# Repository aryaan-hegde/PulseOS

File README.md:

# PulseOS
A smartwatch that can detect, monitor and display your heart rate, show real time and calculate your daily steps. Contains a custom 4-layer, 35 mm circular PCB based on the RP2350B microcontroller with a heart-rate PPG sensor, RTC, IMU and TFT display. The smartwatch features a LiPo battery that can be charged through the PCB via a USB cable. Additionally, the board also contains a switchover mechanism so that you can power the watch solely through USB. Actively reduces battery consumption by turning off peripherals during idle mode (i.e. when stationary state is detected by the IMU).

The board routing can be seen below:

Additionally, a 3D model of this PCB is also shown below:
| Left Image | Right Image |
| :---: | :---: |
|  |

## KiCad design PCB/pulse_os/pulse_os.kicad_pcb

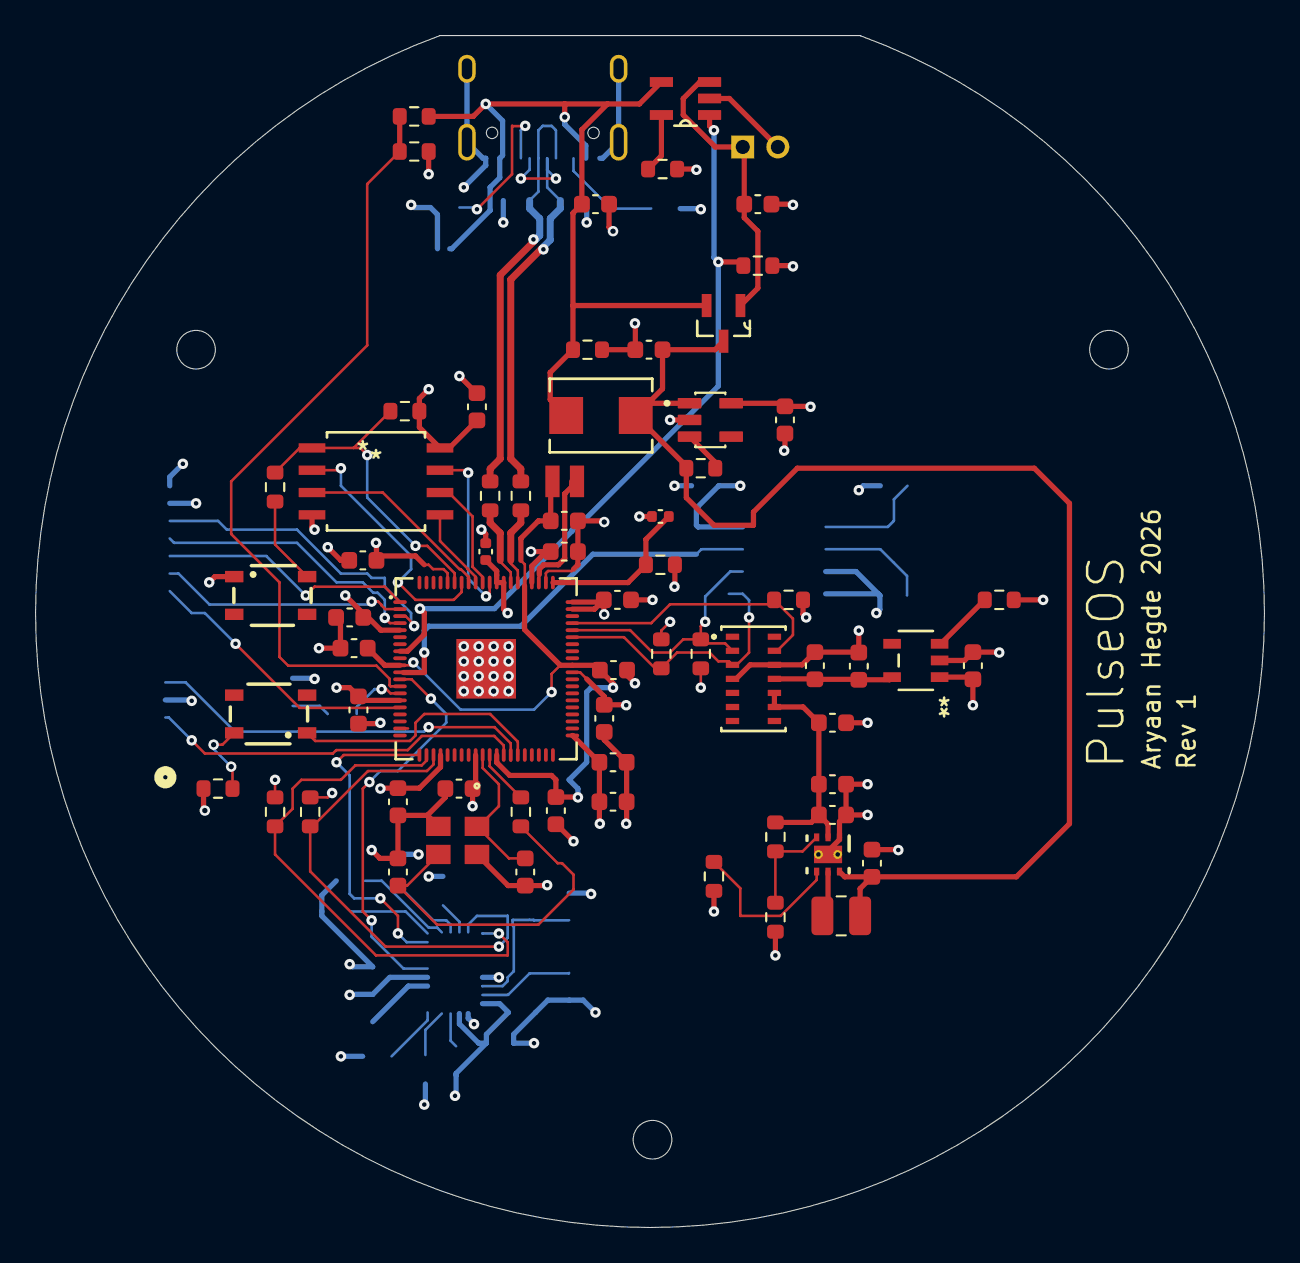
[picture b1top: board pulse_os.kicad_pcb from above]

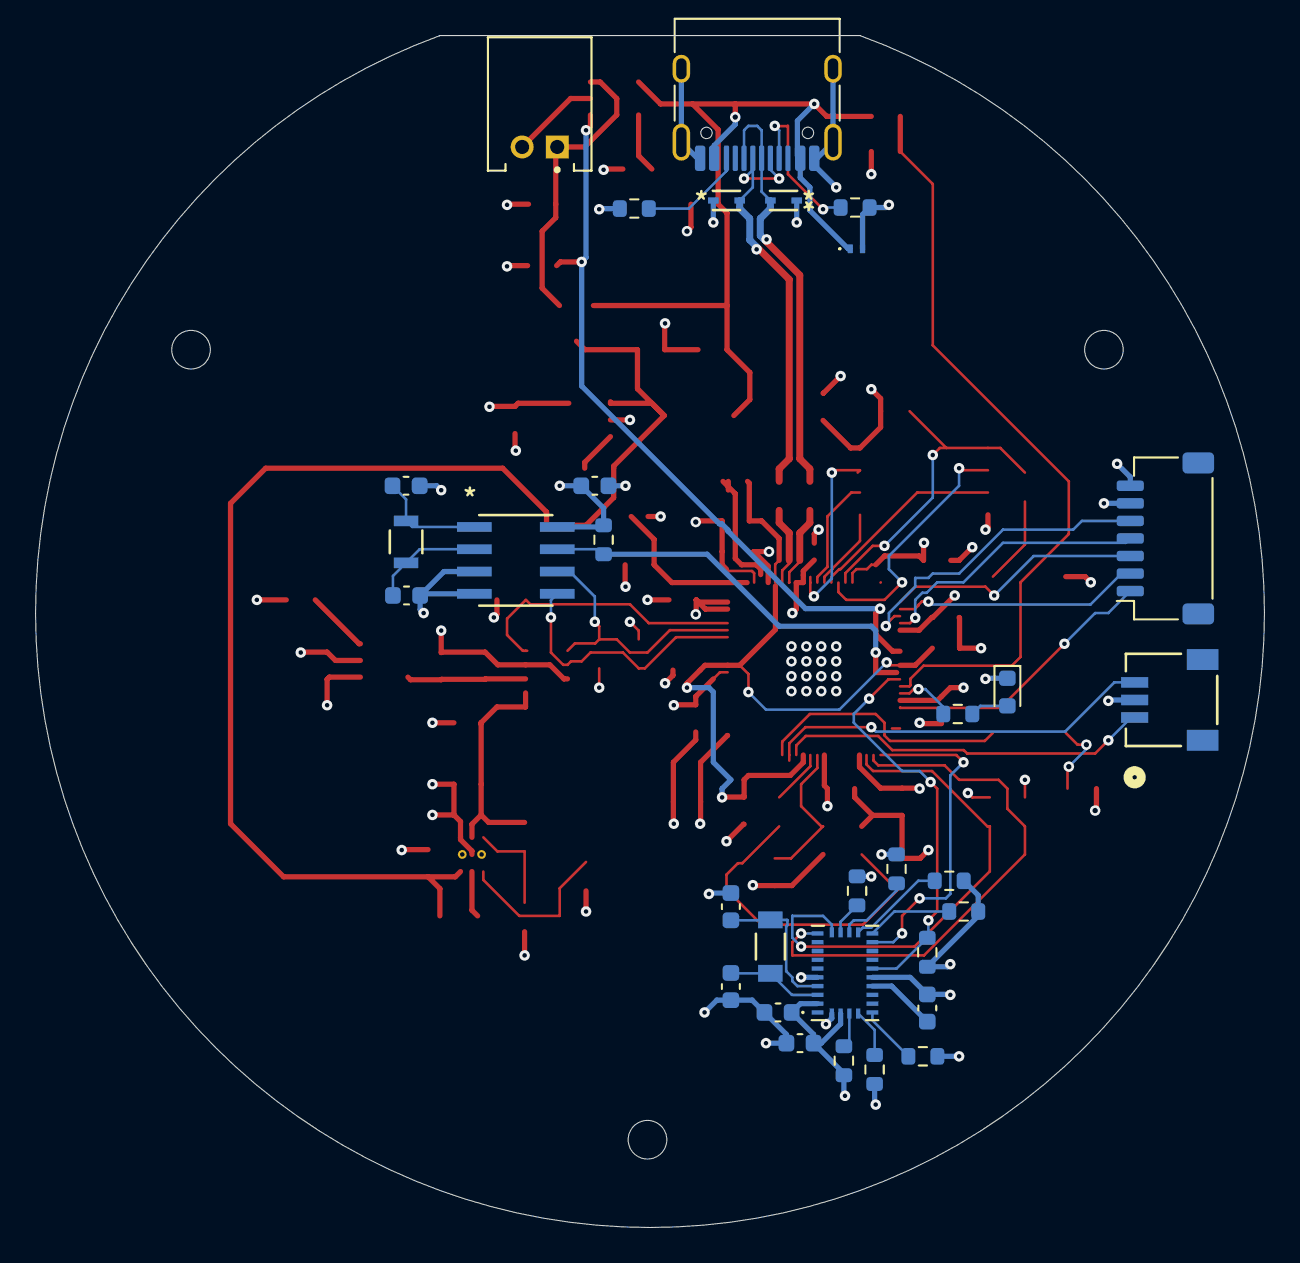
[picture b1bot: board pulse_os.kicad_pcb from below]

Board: 4 copper layers, 70.0 x 67.9 mm, 101 parts (32 on the bottom side), 65 nets.

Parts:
C1, C2, C31, C34, C35, C36, C37, C38: 10uF; C_0603_1608Metric
C3, C6, C8, C11, C13, C14, C15, C17, C18, C19, C20, C21, C27, C28, C29, C39: 100nF; C_0603_1608Metric
C4, C5: 8pF; C_0603_1608Metric
C7, C26: 22pF; C_0603_1608Metric
C9: 4.7u; C_0402_1005Metric
C10, C12, C22: 4.7u; C_0603_1608Metric
C16: 100nF; C_0402_1005Metric
C23: 10u; C_0603_1608Metric
C24, C25: 15pF; C_0603_1608Metric
C30: ABS07-32.768KHZ-T; CAP_ABS07-32.768KHZ-T_ABR
C32, C33: 4.7uF; C_0603_1608Metric
CR1, CR2: ESD321DYAR; SOT5x3_DYA_TEX
CR3: ESD441DPLR; ESD441DPYR
D1: CDBW140-G; CDBB-G
D2: LED; LED_0603_1608Metric
H1, H2, H3: MountingHole; MountingHole_2.2mm_M2
J1: Conn_01x07_Socket; JST_SH_SM07B-SRSS-TB_1x07-1MP_P1.00mm_Horizontal
J2: USB_C_Receptacle_USB2.0_14P; USB_C_Receptacle_HRO_TYPE-C-31-M-12
J3: S2B-PH-K-S; JST_S2B-PH-K-S
J4: SM03B-SRSS-TB; CONN_SM03B-SRSS-TB_JST
L2: 2.2uH; L_1008_2520Metric
L3: AOTA-B201610S3R3-101-T; IND_AOTA-B201610S_2p0x1p6x1p0_ABR
Q1: DMG3415U
R1, R2, R20: 5.1k; R_0603_1608Metric
R5: 33; R_0603_1608Metric
R6, R7, R8, R16, R21, R22, R29, R31, R32, R33, R34, R35, R36, R37, R39: 10k; R_0603_1608Metric
R9, R10, R11, R40: 1k; R_0603_1608Metric
R17, R25: 27; R_0603_1608Metric
R18, R19, R27, R28, R38: 4.7k; R_0603_1608Metric
R23: 1M; R_0603_1608Metric
R24: 249k; R_0603_1608Metric
R26: 100k; R_0603_1608Metric
R30: 15k; R_0603_1608Metric
SW1, SW2: SW_Push; 434133025816
U1: RP2350B; QFN-80_EP_10x10_Pitch0.4mm
U2: AP2112K-3.3; AP2112K_3_3
U4: W25Q128JVS; SOIC_128JVSIQ_WIN
U5: BNO085; IC_BNO085
U6: MCP7940N-xSN; SOIC8-N_MC_MCH
U7: MAX30101EFD+; MAX30101
U8: TPS61099DRVR; DRV0006A
U9: MCP73832T-2ACI_OT; MCP73832T
U10: AP2112K-1.8; AP2112K-1.8TRG1_DIO
X1: ABM8-272-T3; ABM8-272-T3_ABR
XTAL1: ABS07-32.768KHZ-7-T; XTAL_ABS07-32.768KHZ-7-T_ABR

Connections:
+1V1: C8.1, C10.1, C11.1, C22.1, L3.1, U1.10 (DVDD), U1.32 (DVDD), U1.51 (DVDD), U1.65 (VREG_FB)
+1V8: C38.1, C39.1, U7.11 (VDD), U10.5 (VOUT)
+3V3: C2.1, C3.1, C6.1, C12.1, C13.1, C14.1, C15.1, C16.1, C17.1, C18.1, C19.1, C20.1, C21.1, C23.1, C28.1, C29.1, C31.1, J1.7, R5.2, R7.1, R16.1, R18.2, R19.2, R21.2, R22.1, R27.2, R28.2, R31.2, R33.2, R34.2, R37.2, R38.2, R39.2, U1.5 (IOVDD), U1.15 (IOVDD), U1.24 (IOVDD), U1.29 (IOVDD), U1.41 (IOVDD), U1.50 (IOVDD), U1.59 (ADC_AVDD), U1.60 (IOVDD), U1.64 (VREG_VIN), U1.68 (USB_OTP_VDD), U1.69 (QSPI_IOVDD), U1.76 (IOVDD), U2.5 (VOUT), U4.8 (VCC), U5.3 (VDD), U5.28 (VDDIO), U6.8 (VCC), U10.1 (VIN)
+5V: C35.1, C36.1, C37.1, R23.2, U7.9 (VLED+), U7.10 (VLED+), U8.2 (VOUT)
/MCU/INDICATOR_LED: R40.2, U1.14 (GPIO15)
/MCU/QSPI_SCLK: U1.71 (QSPI_SCLK), U4.6 (CLK)
/MCU/QSPI_SD0: U1.72 (QSPI_SD0), U4.5 (DI/IO_{0})
/MCU/QSPI_SD1: U1.74 (QSPI_SD1), U4.2 (DO/IO_{1})
/MCU/QSPI_SD2: U1.73 (QSPI_SD2), U4.3 (~WP/IO_{2})
/MCU/QSPI_SD3: U1.70 (QSPI_SD3), U4.7 (~HOLD/~RESET/IO_{3})
/MCU/QSPI_SS: R7.2, R9.1, U1.75 (~QSPI_SS), U4.1 (~CS)
/MCU/RUN: SW2.1, U1.35 (RUN)
/MCU/SWCLK: J4.1, U1.33 (SWCLK)
/MCU/SWDIO: J4.3, U1.34 (SWDIO)
/MCU/USB_ON: R29.2, R30.1, U1.13 (GPIO14)
/MCU/XIN: C24.1, U1.30 (XIN), X1.1
/MCU/XOUT: R10.2, U1.31 (XOUT)
/Peripherals/BOOTN: R34.1, U5.4 (~BOOT)
/Peripherals/ENV_SCL: R37.1, U5.15 (ENV_SCL)
/Peripherals/ENV_SDA: R39.1, U5.16 (ENV_SDA)
/Peripherals/H_CSN: R31.1, U5.18 (~H_CS)
/Peripherals/PS0: R32.1, U5.6 (PS0/WAKE)
/Peripherals/PS1: R35.1, U5.5 (PS1)
/Peripherals/SA0: R36.1, U5.17 (SA0/H_MOSI)
/Power/D+: CR1.2 (I/O), J2.A6 (D+), J2.B6 (D+), R25.1
/Power/D-: CR2.2 (I/O), J2.A7 (D-), J2.B7 (D-), R17.1
GND: C1.2, C2.2, C3.2, C4.2, C5.2, C6.2, C7.2, C8.2, C9.2, C10.2, C11.2, C12.2, C13.2, C14.2, C15.2, C16.2, C17.2, C18.2, C19.2, C20.2, C21.2, C22.2, C23.2, C24.2, C25.2, C26.2, C27.2, C28.2, C29.2, C31.2, C32.2, C33.2, C34.2, C35.2, C36.2, C37.2, C38.2, C39.2, CR1.1 (GND), CR2.1 (GND), CR3.2 (GND), D2.1 (K), J1.6, J2.A1 (GND), J2.A12 (GND), J2.B1 (GND), J2.B12 (GND), J2.SH (SHIELD), J3.2, J4.2, R1.2, R2.2, R6.2, R11.1, R20.2, R24.1, R26.1, R30.2, R32.2, R35.2, R36.2, SW1.1, U1.62 (VREG_PGND), U1.81 (GND), U2.2 (GND), U4.4 (GND), U5.2 (GND), U5.10 (CLKSEL0), U5.25 (GNDIO), U6.3 (VBAT), U6.4 (VSS), U7.4 (PGND), U7.12 (GND), U8.1 (GND), U8.7 (PAD), U9.2 (VSS), U10.2 (GND), X1.2, X1.4
I2C_BUS0_SCL: R28.1, U1.56 (GPIO45/ADC5), U6.6 (SCL), U7.2 (SCL)
I2C_BUS0_SDA: R27.1, U1.55 (GPIO44/ADC4), U6.5 (SDA), U7.3 (SDA)
I2C_BUS1_SCL: R19.1, U1.23 (GPIO23), U5.19 (H_SCL/SCK/RX)
I2C_BUS1_SDA: R18.1, U1.22 (GPIO22), U5.20 (H_SDA/H_MISO/TX)
IMU_INTN: U1.21 (GPIO21), U5.14 (~H_INT)
IMU_RST: R33.1, U1.12 (GPIO13), U5.11 (~RST)
LCD_CS: J1.2, U1.2 (GPIO5)
LCD_DC: J1.3, U1.1 (GPIO4)
LCD_RST: J1.1, U1.16 (GPIO16)
LCD_SCL: J1.5, U1.3 (GPIO6)
LCD_SDA: J1.4, U1.4 (GPIO7)
MAX_INTN: R38.1, U1.57 (GPIO46/ADC6), U7.13 (*INT)
MFP: R22.2, U1.11 (GPIO12), U6.7 (MFP)
unnamed: C25.1, R10.1, X1.3
unnamed: D2.2 (A), R40.1
unnamed: J2.A5 (CC1), R1.1
unnamed: J2.B5 (CC2), R2.1
unnamed: R9.2, SW1.2
unnamed: R11.2, SW2.2
unnamed: C9.1, R5.1, U1.61 (VREG_AVDD)
unnamed: L3.2, U1.63 (VREG_LX)
unnamed: R8.2, U2.3 (EN)
unnamed: C27.1, U5.9 (CAP)
unnamed: C26.1, C30.1, U5.27 (XIN32)
unnamed: C7.1, C30.2, U5.26 (XOUT32/CLKSEL1)
unnamed: C4.1, U6.1 (X1), XTAL1.1
unnamed: C5.1, U6.2 (X2), XTAL1.2
unnamed: R26.2, U8.4 (EN)
unnamed: R23.1, R24.2, U8.3 (FB)
unnamed: L2.1, U8.5 (SW)
unnamed: R20.1, U9.5 (PROG)
unnamed: R16.2, U10.3 (EN)
STAT: R21.1, U1.8 (GPIO10), U9.1 (STAT)
USB_D+: R25.2, U1.67 (USB_DP)
USB_D-: R17.2, U1.66 (USB_DM)
VBAT: C33.1, J3.1, Q1.1 (D), U9.3 (VBAT)
VBUS: C32.1, CR3.1 (I/O), D1.2 (A), J2.A4 (VBUS), J2.A9 (VBUS), J2.B4 (VBUS), J2.B9 (VBUS), Q1.2 (G), R6.1, R29.1, U9.4 (VDD)
VSWI: C1.1, C34.1, D1.1 (K), L2.2, Q1.3 (S), R8.1, U2.1 (VIN), U8.6 (VIN)

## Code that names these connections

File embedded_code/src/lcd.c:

#include <stdio.h>
#include <math.h>
#include <stdlib.h>
#include <string.h>
#include "pico/stdlib.h"
#include "hardware/spi.h"
#include "LCD_Helpers/image.h"
#include "LCD_Helpers/GUI_Paint.h"

#define LCD_CS 1
#define LCD_SCL 2
#define LCD_SDA 3
#define LCD_DC 0
#define LCD_RST 12

#define GC9A01A_INREGEN2 0xEF
#define GC9A01A_INREGEN1 0xFE
#define GC9A01A_MADCTL 0x36
#define MADCTL_MY 0x80  ///< Bottom to top
#define MADCTL_MX 0x40  ///< Right to left
#define MADCTL_MV 0x20  ///< Reverse Mode
#define MADCTL_ML 0x10  ///< LCD refresh Bottom to top
#define MADCTL_RGB 0x00 ///< Red-Green-Blue pixel order
#define MADCTL_BGR 0x08 ///< Blue-Green-Red pixel order
#define MADCTL_MH 0x04  ///< LCD refresh right to left
#define GC9A01A_COLMOD 0x3A
#define GC9A01A1_POWER1 0xC1   ///< Power Control 1
#define GC9A01A1_POWER2 0xC3   ///< Power Control 2
#define GC9A01A1_POWER3 0xC4   ///< Power Control 3
#define GC9A01A1_POWER4 0xC9   ///< Power Control 4 
#define GC9A01A_GAMMA1 0xF0    ///< Set gamma 1
#define GC9A01A_GAMMA2 0xF1    ///< Set gamma 2
#define GC9A01A_GAMMA3 0xF2    ///< Set gamma 3
#define GC9A01A_GAMMA4 0xF3    ///< Set gamma 4
#define GC9A01A_FRAMERATE 0xE8 ///< Frame rate control
#define GC9A01A_TEON 0x35      ///< Tearing Effect Line ON
#define GC9A01A_INVON 0x21     ///< Display Inversion ON
#define GC9A01A_SLPOUT 0x11    ///< Sleep Out
#define GC9A01A_DISPON 0x29    ///< Display ON

static uint16_t framebuf[240*240];

void init_spi();
void init_display();
void start_init(const uint8_t *start_seq);

static const uint8_t initcmd[] = {
    GC9A01A_INREGEN2, 0,
    0xEB, 1, 0x14, // ?
    GC9A01A_INREGEN1, 0,
    GC9A01A_INREGEN2, 0,
    0xEB, 1, 0x14, // ?
    0x84, 1, 0x40, // ?
    0x85, 1, 0xFF, // ?
    0x86, 1, 0xFF, // ?
    0x87, 1, 0xFF, // ?
    0x88, 1, 0x0A, // ?
    0x89, 1, 0x21, // ?
    0x8A, 1, 0x00, // ?
    0x8B, 1, 0x80, // ?
    0x8C, 1, 0x01, // ?
    0x8D, 1, 0x01, // ?
    0x8E, 1, 0xFF, // ?
    0x8F, 1, 0xFF, // ?
    0xB6, 2, 0x00, 0x00, // ?
    GC9A01A_MADCTL, 1, MADCTL_MX | MADCTL_BGR,
    GC9A01A_COLMOD, 1, 0x05,
    0x90, 4, 0x08, 0x08, 0x08, 0x08, // ?
    0xBD, 1, 0x06, // ?
    0xBC, 1, 0x00, // ?
    0xFF, 3, 0x60, 0x01, 0x04, // ?
    GC9A01A1_POWER2, 1, 0x13,
    GC9A01A1_POWER3, 1, 0x13,
    GC9A01A1_POWER4, 1, 0x22,
    0xBE, 1, 0x11, // ?
    0xE1, 2, 0x10, 0x0E, // ?
    0xDF, 3, 0x21, 0x0c, 0x02, // ?
    GC9A01A_GAMMA1, 6, 0x45, 0x09, 0x08, 0x08, 0x26, 0x2A,
    GC9A01A_GAMMA2, 6, 0x43, 0x70, 0x72, 0x36, 0x37, 0x6F,
    GC9A01A_GAMMA3, 6, 0x45, 0x09, 0x08, 0x08, 0x26, 0x2A,
    GC9A01A_GAMMA4, 6, 0x43, 0x70, 0x72, 0x36, 0x37, 0x6F,
    0xED, 2, 0x1B, 0x0B, // ?
    0xAE, 1, 0x77, // ?
    0xCD, 1, 0x63, // ?
    // Unsure what this line (from manufacturer's boilerplate code) is
    // meant to do, but users reported issues, seems to work OK without:
    //0x70, 9, 0x07, 0x07, 0x04, 0x0E, 0x0F, 0x09, 0x07, 0x08, 0x03, // ?
    GC9A01A_FRAMERATE, 1, 0x34,
    0x62, 12, 0x18, 0x0D, 0x71, 0xED, 0x70, 0x70, // ?
                0x18, 0x0F, 0x71, 0xEF, 0x70, 0x70,
    0x63, 12, 0x18, 0x11, 0x71, 0xF1, 0x70, 0x70, // ?
                0x18, 0x13, 0x71, 0xF3, 0x70, 0x70,
    0x64, 7, 0x28, 0x29, 0xF1, 0x01, 0xF1, 0x00, 0x07, // ?
    0x66, 10, 0x3C, 0x00, 0xCD, 0x67, 0x45, 0x45, 0x10, 0x00, 0x00, 0x00, // ?
    0x67, 10, 0x00, 0x3C, 0x00, 0x00, 0x00, 0x01, 0x54, 0x10, 0x32, 0x98, // ?
    0x74, 7, 0x10, 0x85, 0x80, 0x00, 0x00, 0x4E, 0x00, // ?
    0x98, 2, 0x3e, 0x07, // ?
    GC9A01A_TEON, 0,
    GC9A01A_INVON, 0,
    GC9A01A_SLPOUT, 0x80, // Exit sleep
    GC9A01A_DISPON, 0x80, // Display on
    0x00                  // End of list
};

void init_spi(){
    gpio_set_function(LCD_SDA, GPIO_FUNC_SPI);
    gpio_set_function(LCD_SCL, GPIO_FUNC_SPI);
    spi_init(spi0, 10000000);
    spi_set_format(spi0, 8, 0, 0, SPI_MSB_FIRST);

    gpio_init(LCD_DC);
    gpio_set_dir(LCD_DC, 1);
    gpio_init(LCD_CS);
    gpio_set_dir(LCD_CS, 1);
    gpio_init(LCD_RST);
    gpio_set_dir(LCD_RST, 1);
    
    gpio_put(LCD_CS, 1);
}

void init_display(){
    gpio_put(LCD_RST, 1); sleep_ms(10);
    gpio_put(LCD_RST, 0); sleep_ms(10);
    gpio_put(LCD_RST, 1); sleep_ms(120);
    
    start_init(initcmd);
}

void command_seq(uint8_t cmd, const uint8_t *args, size_t n){
    gpio_put(LCD_CS, 0);
    gpio_put(LCD_DC, 0);                      // command
    spi_write_blocking(spi0, &cmd, 1);
    if (n) {
        gpio_put(LCD_DC, 1);                  // data
        spi_write_blocking(spi0, args, n);
    }
    gpio_put(LCD_CS, 1);
}

void start_init(const uint8_t *start_seq){
    uint8_t cmd;
    while ((cmd = *start_seq++) != 0) {
        uint8_t x = *start_seq++;
        uint8_t n = x & 0x7F;
        command_seq(cmd, start_seq, n);
        start_seq += n;
        if (x & 0x80) sleep_ms(150);
    }
}

void fill_screen(uint16_t color){
    uint8_t col[] = {0, 0, 0, 239};
    uint8_t row[] = {0, 0, 0, 239};
    command_seq(0x2A, col, 4); //column address set
    command_seq(0x2B, row, 4); //row address set

    uint8_t cmd = 0x2C; // memory write
    gpio_put(LCD_CS, 0);
    gpio_put(LCD_DC, 0);
    spi_write_blocking(spi0, &cmd, 1);
    gpio_put(LCD_DC, 1);

    uint8_t px[2] = { color >> 8, color & 0xFF };
    for (int i = 0; i < 240 * 240; i++)
        spi_write_blocking(spi0, px, 2);
    gpio_put(LCD_CS, 1);
}

static void set_window(uint16_t start_x, uint16_t start_y, uint16_t end_x, uint16_t end_y){
    uint8_t col[] = {start_x >> 8, start_x & 0xFF, end_x >>8, end_x & 0xFF};
    uint8_t row[] = {start_y >> 8, start_y & 0xFF, end_y >>8, end_y & 0xFF};
    command_seq(0x2A, col, 4);
    command_seq(0x2B, row, 4);
}

void flush_screen(void){
    set_window(0,0,239,239);
    command_seq(0x2C, (const uint8_t *)framebuf, sizeof(framebuf));
}

void display_image(const unsigned char *image, uint16_t x, uint16_t y, uint16_t w, uint16_t h){
    uint8_t cmd = 0x2c; //memory write 
    set_window(x, y, x+w-1, y+h-1);
    command_seq(cmd, image, (size_t)(w*h*2));
}

void turnoff_seq(){
    gpio_put(LCD_CS, 0);
    gpio_put(LCD_DC, 0);
    uint8_t turnoff_cmd = 0x28;
    spi_write_blocking(spi0, &turnoff_cmd, 1);
    gpio_put(LCD_CS, 1);
}

void DrawHeart(uint16_t color){
    Paint_NewImage(framebuf, 240, 240, 0, 0, 16);
    //Paint_Clear(0x0000);
    Paint_DrawCircle(90, 90, 20, color, 5, DRAW_FILL_FULL);
    Paint_DrawCircle(125, 90, 20, color, 5, DRAW_FILL_FULL);
    Paint_DrawCircle(90, 85, 20, color, 5, DRAW_FILL_FULL);
    Paint_DrawCircle(125, 85, 20, color, 5, DRAW_FILL_FULL);
    Paint_DrawCircle(108, 95, 10, color, 5, DRAW_FILL_FULL);
    Paint_DrawLine(80, 90, 108, 130, color, 11, LINE_STYLE_SOLID);
    Paint_DrawLine(135, 90, 108, 130, color, 11, LINE_STYLE_SOLID);
    flush_screen();
}

void HeartWave(){
    
}

void lcd_init(void){
    init_spi();
    init_display();
    Paint_NewImage(framebuf, 240, 240, 0, 0, 16);
}

// int main(){
    // init_spi();
    // init_display();
    
    // Paint_NewImage(framebuf, 240, 240, 0, 0, 16);
    // Paint_Clear(0x0000);
    // //Paint_DrawString_EN(40, 180, "Shubh is so cute", &Font16, 0x0000, 0xFFFF);
    // Paint_DrawTime(90, 90, , &Font24, RED, BLACK);
    // // sleep_ms(5000);
    // // for(;;){
    // //     DrawHeart(RED);
    // //     sleep_ms(1500);
    // //     DrawHeart(BLUE);
    // //     sleep_ms(500);
    // // }
    // for(;;){}
    // return 0;
// }

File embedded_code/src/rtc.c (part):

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#define REG_SRAM      0x20  // 64 bytes of battery-backed RAM (0x20-0x5F)

// ---- Bits inside those registers ------------------------------------------
#define SEC_ST          0x80  // 1 = run the oscillator (the clock counts)
#define HOUR_12H        0x40  // 1 = 12 hour mode, 0 = 24 hour mode
#define WKDAY_OSCRUN    0x20  // read only: 1 = the crystal is really ticking
#define WKDAY_PWRFAIL   0x10  // 1 = main power was lost (write 0 to clear)
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        printf("[RTC] MCP7940N not found at 0x%02X on I2C%u (SDA=GP%u, SCL=GP%u). "
               "Check wiring, 3.3 V power and pull-up resistors. Retrying...\n",
               RTC_I2C_ADDR, i2c_get_index(RTC_I2C_PORT),
               i2c_get_index(RTC_I2C_PORT) ? I2C_BUS1_SDA_PIN : I2C_BUS0_SDA_PIN,
               i2c_get_index(RTC_I2C_PORT) ? I2C_BUS1_SCL_PIN : I2C_BUS0_SCL_PIN);
        return false;
    }

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

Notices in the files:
parts and their libraries:
License: Apache-2.0
